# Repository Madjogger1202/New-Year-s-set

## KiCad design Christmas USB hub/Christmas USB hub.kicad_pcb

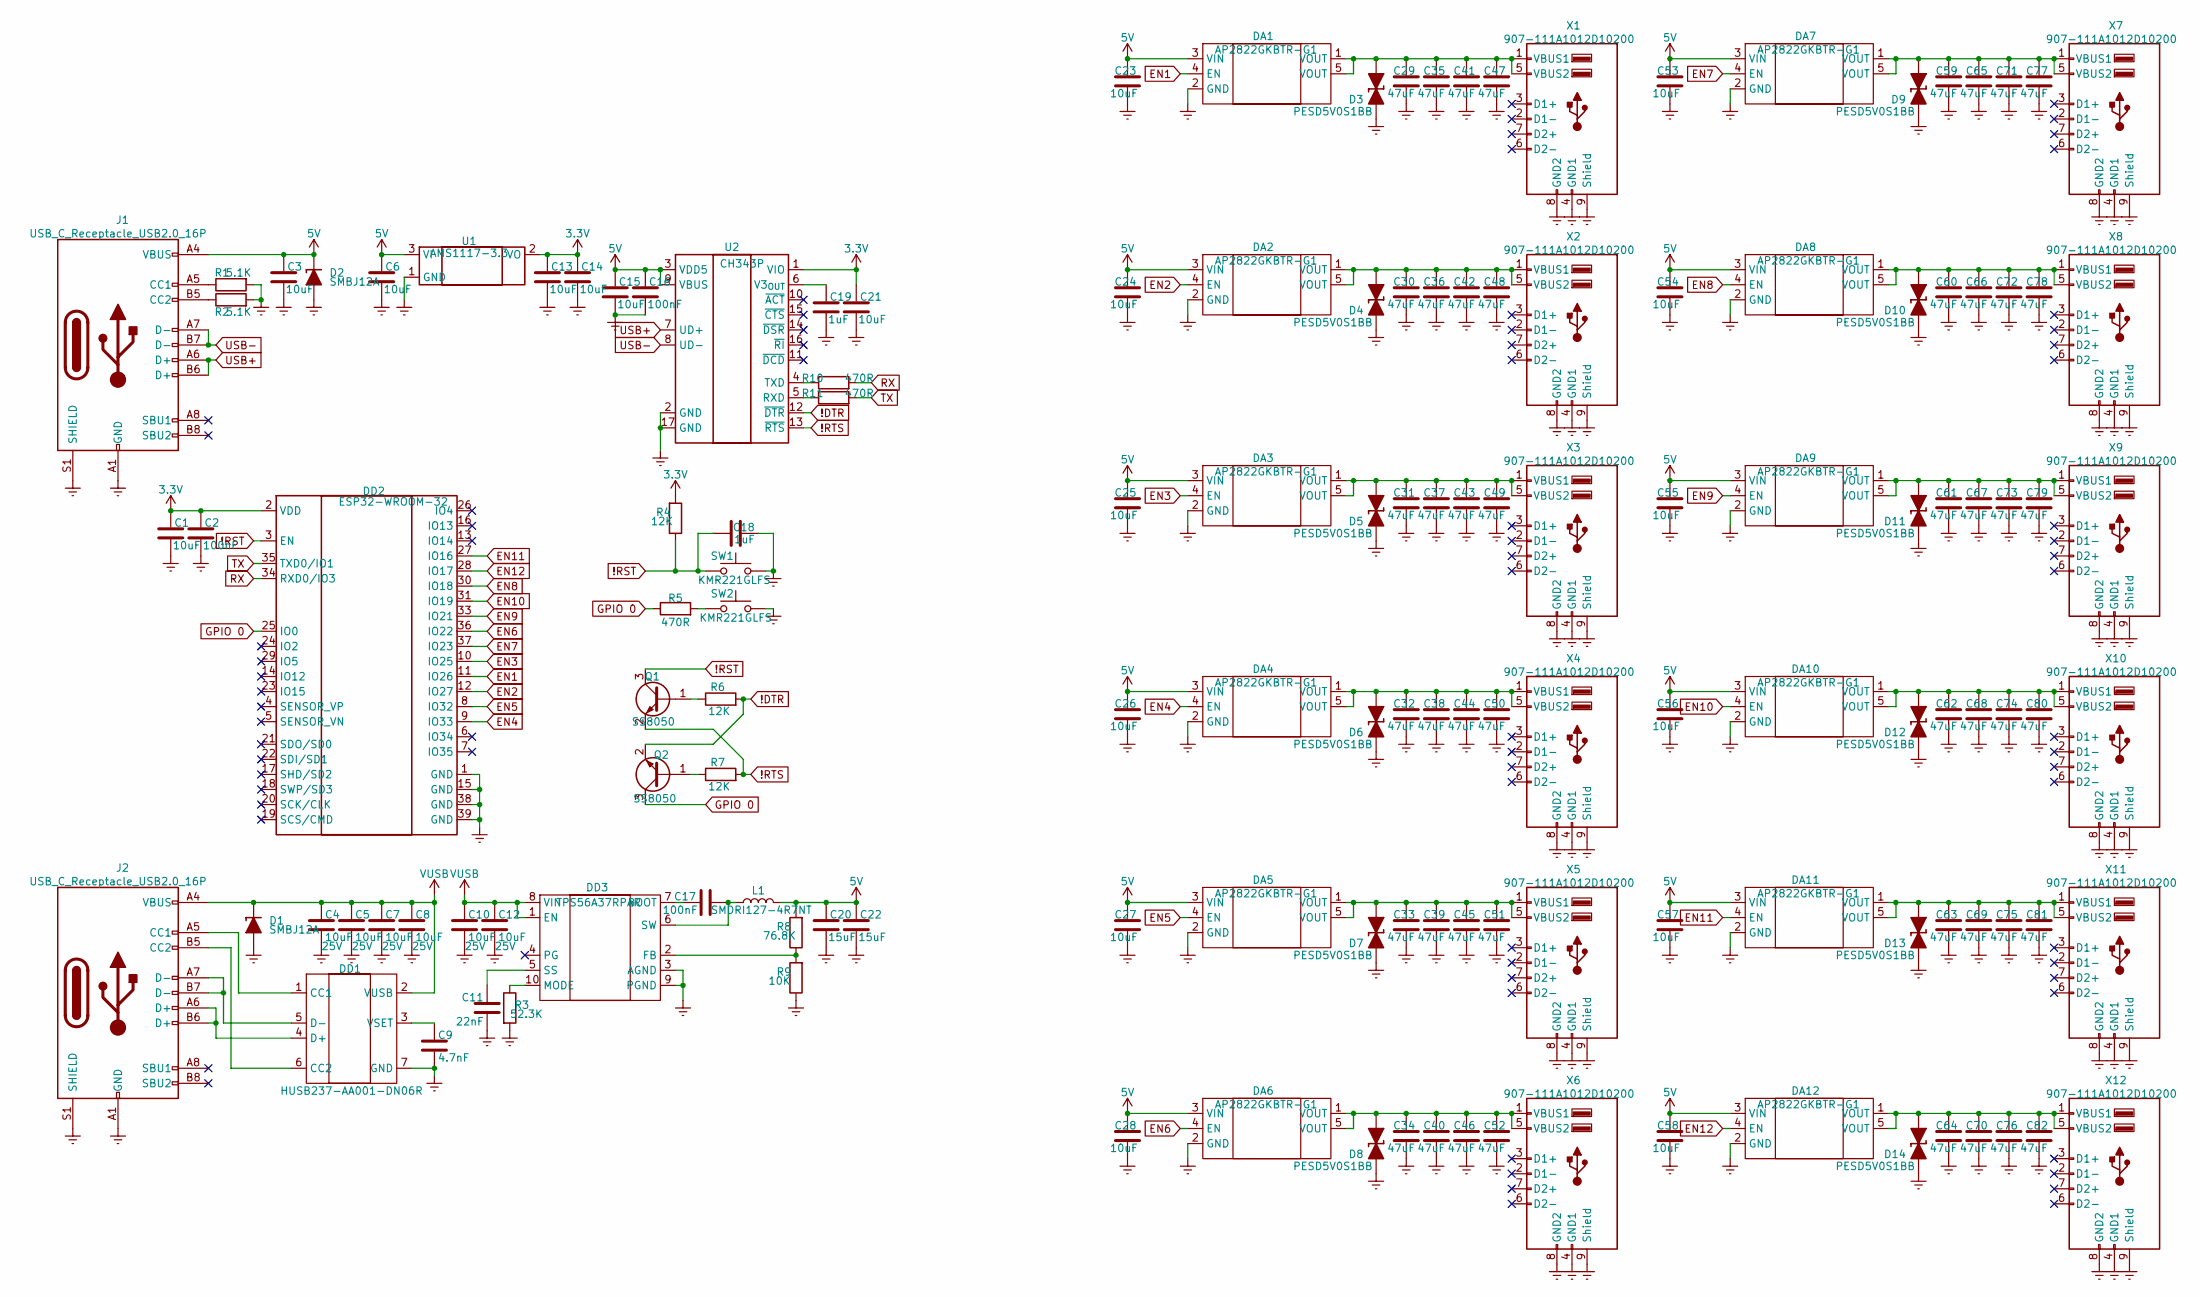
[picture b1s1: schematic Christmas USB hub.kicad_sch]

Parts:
C1, C3, C6, C13, C14, C15, C21, C23, C24, C25, C26, C27, C28, C53, C54, C55, C56, C57, C58: 10uF; C_0402_1005Metric
C2, C16, C17: 100nF; C_0402_1005Metric
C4, C5, C7, C8, C10, C12: 10uF; C_0805_2012Metric; Voltage 25V; JLCPCB part C5674
C9: 4.7nF; C_0402_1005Metric; JLCPCB part C5674
C11: 22nF; C_0402_1005Metric
C18, C19: 1uF; C_0402_1005Metric
C20, C22: 15uF; C_0402_1005Metric
C29, C30, C31, C32, C33, C34, C35, C36, C37, C38, C39, C40, C41, C42, C43, C44, C45, C46, C47, C48, C49, C50, C51, C52, C59, C60, C61, C62, C63, C64, C65, C66, C67, C68, C69, C70, C71, C72, C73, C74, C75, C76, C77, C78, C79, C80, C81, C82: 47uF; C_0603_1608Metric
D1, D2: SMBJ12A; D_SMB
D3, D4, D5, D6, D7, D8, D9, D10, D11, D12, D13, D14: PESD5V0S1BB; D_SOD-523_TVS
DA1, DA2, DA3, DA4, DA5, DA6, DA7, DA8, DA9, DA10, DA11, DA12: AP2822GKBTR-G1; SOT-23-5
DD1: HUSB237-AA001-DN06R; Manufacturer Part HUSB237-AA001-DN06R; LCSC Part Name HUSB237-AA001-DN06R
DD2: ESP32-WROOM-32
DD3: TPS56A37RPAR; Manufacturer Part TPS56A37RPAR; LCSC Part Name TPS56A37RPAR
J1, J2: USB_C_Receptacle_USB2.0_16P; USB_C_Receptacle_GCT_USB4105-xx-A_16P_TopMnt_Horizontal
L1: SMDRI127-4R7NT; L_SXN_SMDRI127
Q1, Q2: SS8050; SOT-23
R1, R2: 5.1K; R_0402_1005Metric
R3: 52.3K; R_0402_1005Metric
R4, R6, R7: 12K; R_0402_1005Metric
R5, R10, R11: 470R; R_0402_1005Metric
R8: 76.8K; R_0402_1005Metric
R9: 10K; R_0402_1005Metric
SW1, SW2: KMR221GLFS; SW_SPST_PTS810
U1: AMS1117-3.3; SOT-89-3
U2: CH343P; WCH_QFN-16-1EP_3x3mm_P0.5mm_EP1.8x1.8mm
X1, X2, X3, X4, X5, X6, X7, X8, X9, X10, X11, X12: 907-111A1012D10200; USB_A_CUI_UJ2-ADH-TH_Horizontal_Stacked

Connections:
3.3V: C1.1, C2.1, C13.1, C14.1, C21.1, DD2.2 (VDD), R4.2, U1.2 (VO), U2.1 (VIO)
5V: C3.1, C6.1, C15.1, C16.1, C20.1, C22.1, C23.1, C24.1, C25.1, C26.1, C27.1, C28.1, C53.1, C54.1, C55.1, C56.1, C57.1, C58.1, D2.1 (K), DA1.3 (VIN), DA2.3 (VIN), DA3.3 (VIN), DA4.3 (VIN), DA5.3 (VIN), DA6.3 (VIN), DA7.3 (VIN), DA8.3 (VIN), DA9.3 (VIN), DA10.3 (VIN), DA11.3 (VIN), DA12.3 (VIN), J1.A4 (VBUS), J1.A9 (VBUS), J1.B4 (VBUS), J1.B9 (VBUS), L1.2, R8.2, U1.3 (VI), U2.3 (VDD5), U2.9 (VBUS)
!DTR: Q2.2 (E), R6.2, U2.12 (~DTR)
!RST: C18.1, DD2.3 (EN), Q1.3 (C), R4.1, SW1.2
!RTS: Q1.2 (E), R7.2, U2.13 (~RTS)
EN1: DA1.4 (EN), DD2.11 (IO26)
EN2: DA2.4 (EN), DD2.12 (IO27)
EN3: DA3.4 (EN), DD2.10 (IO25)
EN4: DA4.4 (EN), DD2.9 (IO33)
EN5: DA5.4 (EN), DD2.8 (IO32)
EN6: DA6.4 (EN), DD2.36 (IO22)
EN7: DA7.4 (EN), DD2.37 (IO23)
EN8: DA8.4 (EN), DD2.30 (IO18)
EN9: DA9.4 (EN), DD2.33 (IO21)
EN10: DA10.4 (EN), DD2.31 (IO19)
EN11: DA11.4 (EN), DD2.27 (IO16)
EN12: DA12.4 (EN), DD2.28 (IO17)
Earth: C1.2, C2.2, C3.2, C4.2, C5.2, C6.2, C7.2, C8.2, C9.2, C10.2, C11.1, C12.2, C13.2, C14.2, C15.2, C16.2, C18.2, C19.2, C20.2, C21.2, C22.2, C23.2, C24.2, C25.2, C26.2, C27.2, C28.2, C29.2, C30.2, C31.2, C32.2, C33.2, C34.2, C35.2, C36.2, C37.2, C38.2, C39.2, C40.2, C41.2, C42.2, C43.2, C44.2, C45.2, C46.2, C47.2, C48.2, C49.2, C50.2, C51.2, C52.2, C53.2, C54.2, C55.2, C56.2, C57.2, C58.2, C59.2, C60.2, C61.2, C62.2, C63.2, C64.2, C65.2, C66.2, C67.2, C68.2, C69.2, C70.2, C71.2, C72.2, C73.2, C74.2, C75.2, C76.2, C77.2, C78.2, C79.2, C80.2, C81.2, C82.2, D1.2 (A), D2.2 (A), D3.1 (K), D4.1 (K), D5.1 (K), D6.1 (K), D7.1 (K), D8.1 (K), D9.1 (K), D10.1 (K), D11.1 (K), D12.1 (K), D13.1 (K), D14.1 (K), DA1.2 (GND), DA2.2 (GND), DA3.2 (GND), DA4.2 (GND), DA5.2 (GND), DA6.2 (GND), DA7.2 (GND), DA8.2 (GND), DA9.2 (GND), DA10.2 (GND), DA11.2 (GND), DA12.2 (GND), DD1.7 (GND), DD2.1 (GND), DD2.15 (GND), DD2.38 (GND), DD2.39 (GND), DD3.3 (AGND), DD3.9 (PGND), J1.A1 (GND), J1.A12 (GND), J1.B1 (GND), J1.B12 (GND), J1.S1 (SHIELD), J2.A1 (GND), J2.A12 (GND), J2.B1 (GND), J2.B12 (GND), J2.S1 (SHIELD), R1.2, R2.2, R3.2, R9.1, SW1.1, SW2.1, U1.1 (GND), U2.2 (GND), U2.17 (GND), X1.4 (GND1), X1.8 (GND2), X1.9 (Shield), X2.4 (GND1), X2.8 (GND2), X2.9 (Shield), X3.4 (GND1), X3.8 (GND2), X3.9 (Shield), X4.4 (GND1), X4.8 (GND2), X4.9 (Shield), X5.4 (GND1), X5.8 (GND2), X5.9 (Shield), X6.4 (GND1), X6.8 (GND2), X6.9 (Shield), X7.4 (GND1), X7.8 (GND2), X7.9 (Shield), X8.4 (GND1), X8.8 (GND2), X8.9 (Shield), X9.4 (GND1), X9.8 (GND2), X9.9 (Shield), X10.4 (GND1), X10.8 (GND2), X10.9 (Shield), X11.4 (GND1), X11.8 (GND2), X11.9 (Shield), X12.4 (GND1), X12.8 (GND2), X12.9 (Shield)
GPIO 0: DD2.25 (IO0), Q2.3 (C), R5.1
unnamed: C29.1, C35.1, C41.1, C47.1, D3.2 (A), DA1.1 (VOUT), DA1.5 (VOUT), X1.1 (VBUS1), X1.5 (VBUS2)
unnamed: C30.1, C36.1, C42.1, C48.1, D4.2 (A), DA2.1 (VOUT), DA2.5 (VOUT), X2.1 (VBUS1), X2.5 (VBUS2)
unnamed: C31.1, C37.1, C43.1, C49.1, D5.2 (A), DA3.1 (VOUT), DA3.5 (VOUT), X3.1 (VBUS1), X3.5 (VBUS2)
unnamed: C32.1, C38.1, C44.1, C50.1, D6.2 (A), DA4.1 (VOUT), DA4.5 (VOUT), X4.1 (VBUS1), X4.5 (VBUS2)
unnamed: C33.1, C39.1, C45.1, C51.1, D7.2 (A), DA5.1 (VOUT), DA5.5 (VOUT), X5.1 (VBUS1), X5.5 (VBUS2)
unnamed: C34.1, C40.1, C46.1, C52.1, D8.2 (A), DA6.1 (VOUT), DA6.5 (VOUT), X6.1 (VBUS1), X6.5 (VBUS2)
unnamed: C59.1, C65.1, C71.1, C77.1, D9.2 (A), DA7.1 (VOUT), DA7.5 (VOUT), X7.1 (VBUS1), X7.5 (VBUS2)
unnamed: C60.1, C66.1, C72.1, C78.1, D10.2 (A), DA8.1 (VOUT), DA8.5 (VOUT), X8.1 (VBUS1), X8.5 (VBUS2)
unnamed: C61.1, C67.1, C73.1, C79.1, D11.2 (A), DA9.1 (VOUT), DA9.5 (VOUT), X9.1 (VBUS1), X9.5 (VBUS2)
unnamed: C62.1, C68.1, C74.1, C80.1, D12.2 (A), DA10.1 (VOUT), DA10.5 (VOUT), X10.1 (VBUS1), X10.5 (VBUS2)
unnamed: C63.1, C69.1, C75.1, C81.1, D13.2 (A), DA11.1 (VOUT), DA11.5 (VOUT), X11.1 (VBUS1), X11.5 (VBUS2)
unnamed: C64.1, C70.1, C76.1, C82.1, D14.2 (A), DA12.1 (VOUT), DA12.5 (VOUT), X12.1 (VBUS1), X12.5 (VBUS2)
unnamed: DD1.1 (CC1), J2.A5 (CC1)
unnamed: DD1.6 (CC2), J2.B5 (CC2)
unnamed: DD1.4 (D+), J2.A6 (D+), J2.B6 (D+)
unnamed: DD1.5 (D-), J2.A7 (D-), J2.B7 (D-)
unnamed: C9.1, DD1.3 (VSET)
unnamed: C17.1, DD3.7 (BOOT)
unnamed: DD3.2 (FB), R8.1, R9.2
unnamed: DD3.10 (MODE), R3.1
unnamed: C11.2, DD3.5 (SS)
unnamed: C17.2, DD3.6 (SW), L1.1
unnamed: J1.A5 (CC1), R1.1
unnamed: J1.B5 (CC2), R2.1
unnamed: Q1.1 (B), R6.1
unnamed: Q2.1 (B), R7.1
unnamed: R5.2, SW2.2
unnamed: R11.1, U2.5 (RXD)
unnamed: R10.1, U2.4 (TXD)
unnamed: C19.1, U2.6 (V3_{OUT})
RX: DD2.34 (RXD0/IO3), R10.2
TX: DD2.35 (TXD0/IO1), R11.2
USB+: J1.A6 (D+), J1.B6 (D+), U2.7 (UD+)
USB-: J1.A7 (D-), J1.B7 (D-), U2.8 (UD-)
VUSB: C4.1, C5.1, C7.1, C8.1, C10.1, C12.1, D1.1 (K), DD1.2 (VUSB), DD3.1 (EN), DD3.8 (VIN), J2.A4 (VBUS), J2.A9 (VBUS), J2.B4 (VBUS), J2.B9 (VBUS)

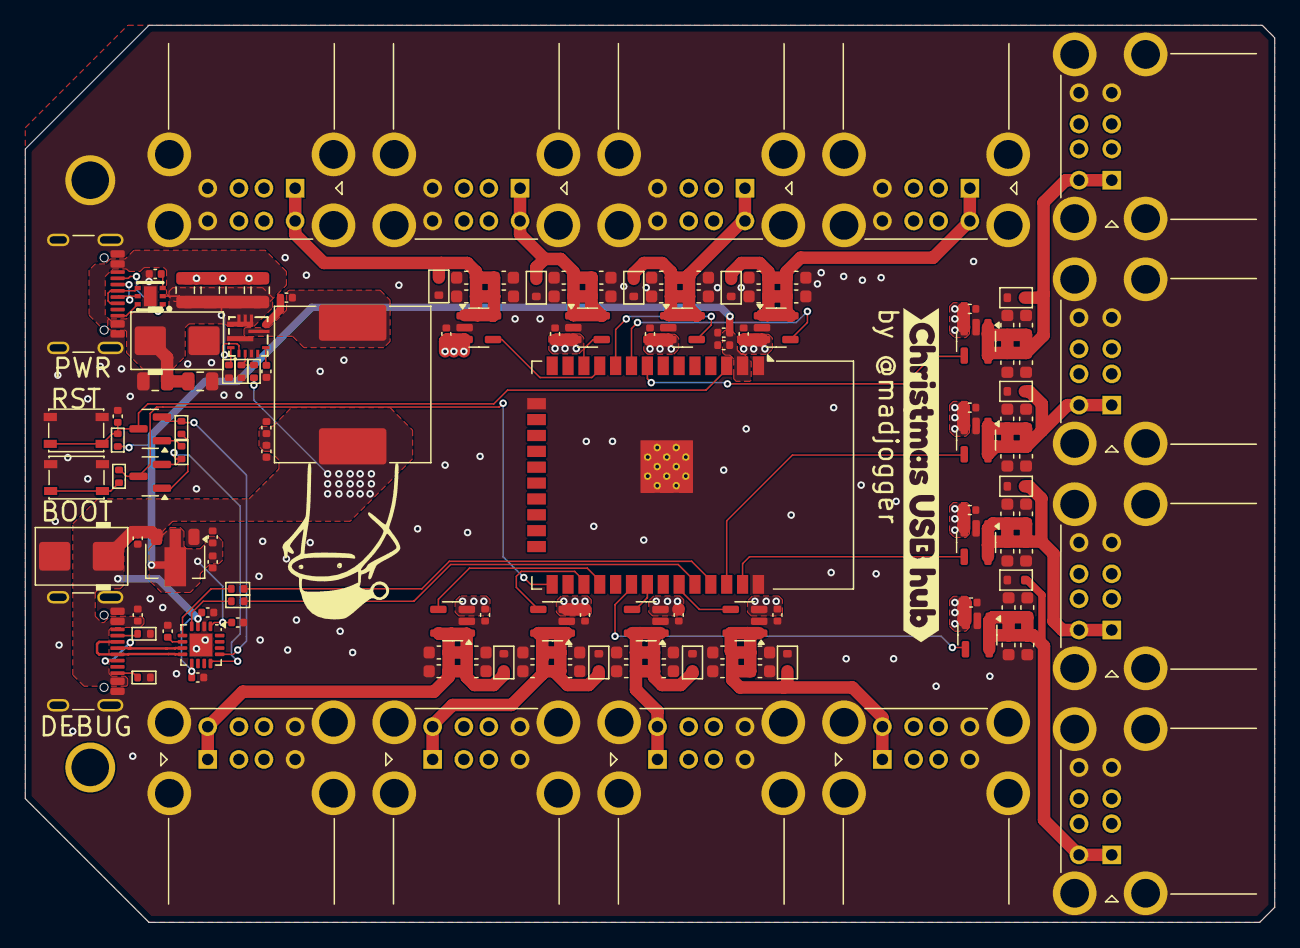
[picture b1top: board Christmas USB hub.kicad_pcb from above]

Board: 2 copper layers, 100.0 x 71.8 mm, 144 parts (0 on the bottom side), 54 nets.

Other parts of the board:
kibuzzard-69519964: G***; kibuzzard-69519964

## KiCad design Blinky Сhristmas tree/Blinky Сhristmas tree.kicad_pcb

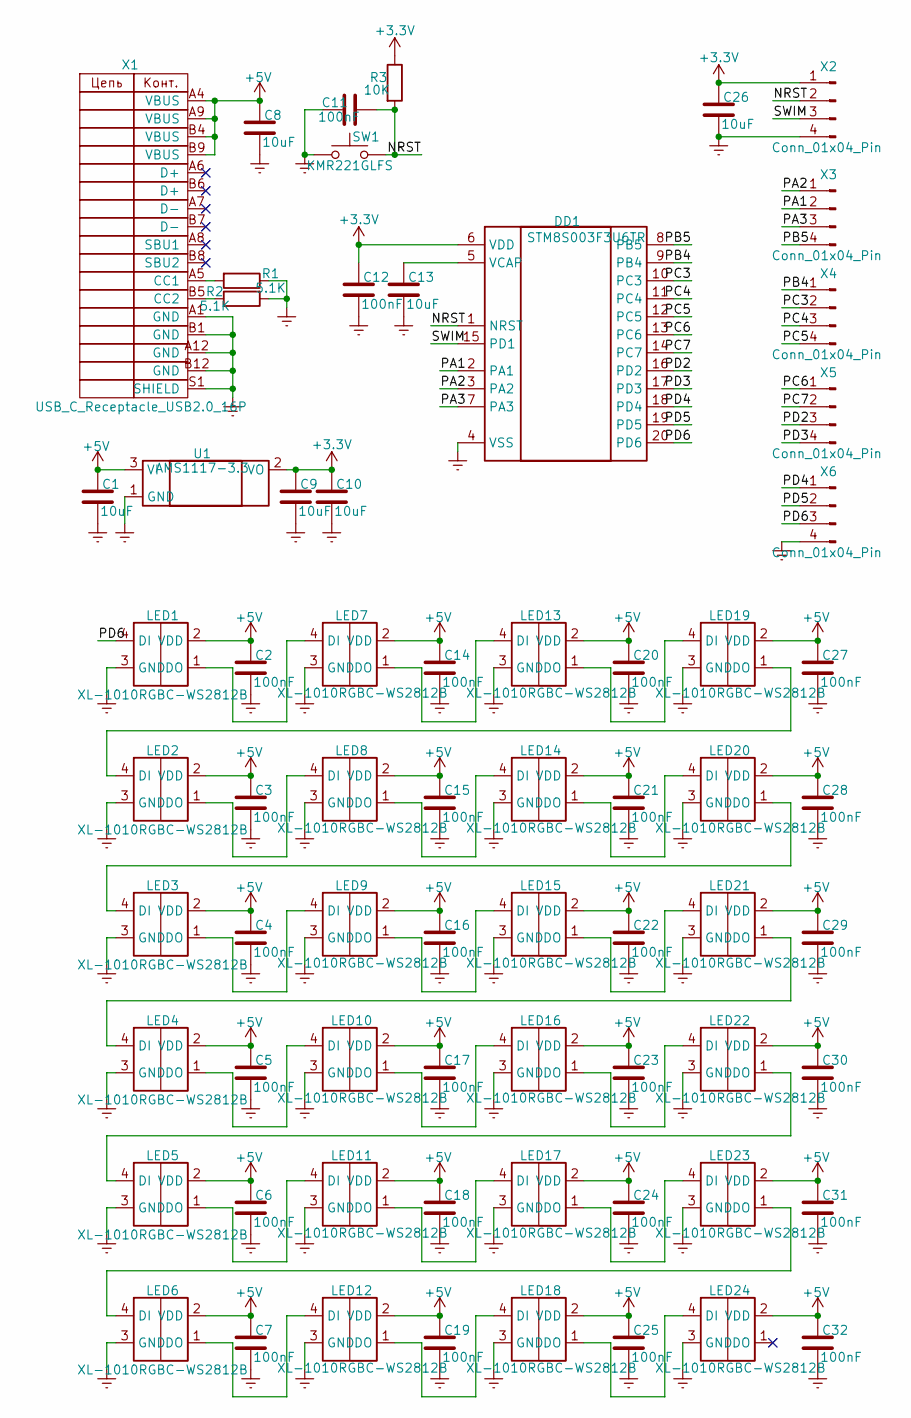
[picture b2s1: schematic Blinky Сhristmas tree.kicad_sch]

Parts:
C1, C8, C9, C10, C13, C26: 10uF; C_0402_1005Metric
C2, C3, C4, C5, C6, C7, C11, C12, C14, C15, C16, C17, C18, C19, C20, C21, C22, C23, C24, C25, C27, C28, C29, C30, C31, C32: 100nF; C_0402_1005Metric
DD1: STM8S003F3U6TR; ST_UFQFPN-20_3x3mm_P0.5mm
LED1, LED2, LED3, LED4, LED5, LED6, LED7, LED8, LED9, LED10, LED11, LED12, LED13, LED14, LED15, LED16, LED17, LED18, LED19, LED20, LED21, LED22, LED23, LED24: XL-1010RGBC-WS2812B; XL1010RGBCWS2812B; Manufacturer_Part_Number XL-1010RGBC-WS2812B
R1, R2: 5.1K; R_0402_1005Metric
R3: 10K; R_0402_1005Metric
SW1: KMR221GLFS; SW_SPST_PTS810
U1: AMS1117-3.3; SOT-89-3
X1: USB_C_Receptacle_USB2.0_16P; USB_C_Receptacle_GCT_USB4105-xx-A_16P_TopMnt_Horizontal
X2, X3, X4, X5, X6: Conn_01x04_Pin; PinHeader_1x04_P2.54mm_Vertical

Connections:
+3.3V: C9.1, C10.1, C12.1, C26.1, DD1.6 (VDD), R3.1, U1.2 (VO), X2.1
+5V: C1.1, C2.1, C3.1, C4.1, C5.1, C6.1, C7.1, C8.1, C14.1, C15.1, C16.1, C17.1, C18.1, C19.1, C20.1, C21.1, C22.1, C23.1, C24.1, C25.1, C27.1, C28.1, C29.1, C30.1, C31.1, C32.1, LED1.2 (VDD), LED2.2 (VDD), LED3.2 (VDD), LED4.2 (VDD), LED5.2 (VDD), LED6.2 (VDD), LED7.2 (VDD), LED8.2 (VDD), LED9.2 (VDD), LED10.2 (VDD), LED11.2 (VDD), LED12.2 (VDD), LED13.2 (VDD), LED14.2 (VDD), LED15.2 (VDD), LED16.2 (VDD), LED17.2 (VDD), LED18.2 (VDD), LED19.2 (VDD), LED20.2 (VDD), LED21.2 (VDD), LED22.2 (VDD), LED23.2 (VDD), LED24.2 (VDD), U1.3 (VI), X1.A4 (VBUS), X1.A9 (VBUS), X1.B4 (VBUS), X1.B9 (VBUS)
/NRST: C11.1, DD1.1 (NRST), R3.2, SW1.2, X2.2
/PA1: DD1.2 (PA1), X3.2
/PA2: DD1.3 (PA2), X3.1
/PA3: DD1.7 (PA3), X3.3
/PB4: DD1.9 (PB4), X4.1
/PB5: DD1.8 (PB5), X3.4
/PD2: DD1.16 (PD2), X5.3
/PD3: DD1.17 (PD3), X5.4
/PD4: DD1.18 (PD4), X6.1
/PD5: DD1.19 (PD5), X6.2
/PD6: DD1.20 (PD6), LED1.4 (DI), X6.3
/PС3: DD1.10 (PC3), X4.2
/PС4: DD1.11 (PC4), X4.3
/PС5: DD1.12 (PC5), X4.4
/PС6: DD1.13 (PC6), X5.1
/PС7: DD1.14 (PC7), X5.2
/SWIM: DD1.15 (PD1), X2.3
Earth: C1.2, C2.2, C3.2, C4.2, C5.2, C6.2, C7.2, C8.2, C9.2, C10.2, C11.2, C12.2, C13.2, C14.2, C15.2, C16.2, C17.2, C18.2, C19.2, C20.2, C21.2, C22.2, C23.2, C24.2, C25.2, C26.2, C27.2, C28.2, C29.2, C30.2, C31.2, C32.2, DD1.4 (VSS), LED1.3 (GND), LED2.3 (GND), LED3.3 (GND), LED4.3 (GND), LED5.3 (GND), LED6.3 (GND), LED7.3 (GND), LED8.3 (GND), LED9.3 (GND), LED10.3 (GND), LED11.3 (GND), LED12.3 (GND), LED13.3 (GND), LED14.3 (GND), LED15.3 (GND), LED16.3 (GND), LED17.3 (GND), LED18.3 (GND), LED19.3 (GND), LED20.3 (GND), LED21.3 (GND), LED22.3 (GND), LED23.3 (GND), LED24.3 (GND), R1.1, R2.2, SW1.1, U1.1 (GND), X1.A1 (GND), X1.A12 (GND), X1.B1 (GND), X1.B12 (GND), X1.S1 (SHIELD), X2.4, X6.4
unnamed: C13.1, DD1.5 (VCAP)
unnamed: LED1.1 (DO), LED7.4 (DI)
unnamed: LED2.1 (DO), LED8.4 (DI)
unnamed: LED3.1 (DO), LED9.4 (DI)
unnamed: LED4.1 (DO), LED10.4 (DI)
unnamed: LED10.1 (DO), LED16.4 (DI)
unnamed: LED5.1 (DO), LED11.4 (DI)
unnamed: LED11.1 (DO), LED17.4 (DI)
unnamed: LED6.1 (DO), LED12.4 (DI)
unnamed: LED12.1 (DO), LED18.4 (DI)
unnamed: LED7.1 (DO), LED13.4 (DI)
unnamed: LED13.1 (DO), LED19.4 (DI)
unnamed: LED8.1 (DO), LED14.4 (DI)
unnamed: LED14.1 (DO), LED20.4 (DI)
unnamed: LED9.1 (DO), LED15.4 (DI)
unnamed: LED15.1 (DO), LED21.4 (DI)
unnamed: LED16.1 (DO), LED22.4 (DI)
unnamed: LED17.1 (DO), LED23.4 (DI)
unnamed: LED18.1 (DO), LED24.4 (DI)
unnamed: LED2.4 (DI), LED19.1 (DO)
unnamed: LED3.4 (DI), LED20.1 (DO)
unnamed: LED4.4 (DI), LED21.1 (DO)
unnamed: LED5.4 (DI), LED22.1 (DO)
unnamed: LED6.4 (DI), LED23.1 (DO)
unnamed: R1.2, X1.A5 (CC1)
unnamed: R2.1, X1.B5 (CC2)

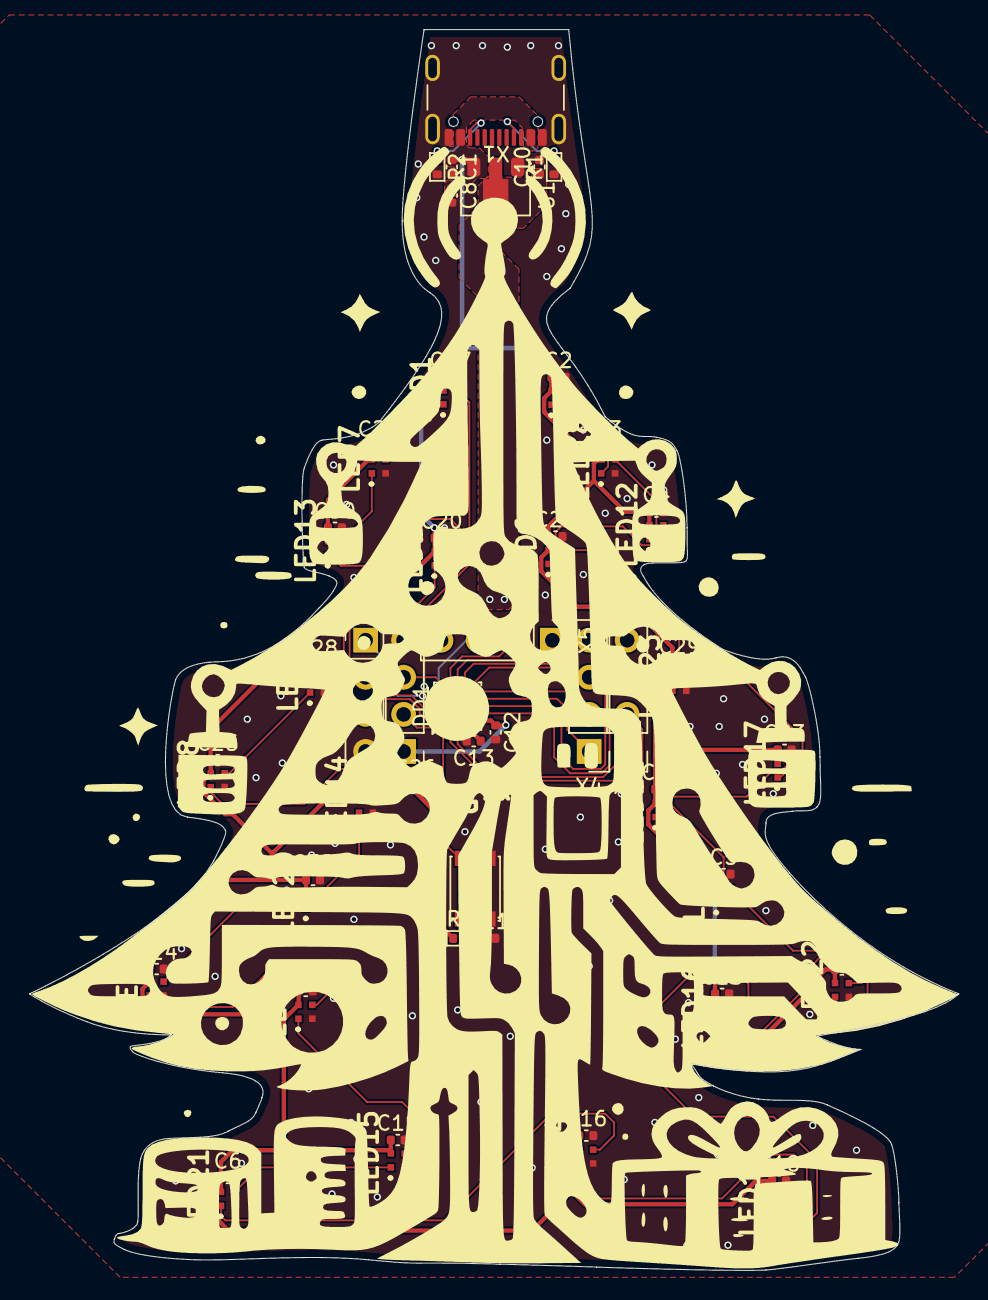
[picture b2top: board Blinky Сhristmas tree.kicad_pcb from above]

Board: 2 copper layers, 63.6 x 84.9 mm, 68 parts (0 on the bottom side), 46 nets.

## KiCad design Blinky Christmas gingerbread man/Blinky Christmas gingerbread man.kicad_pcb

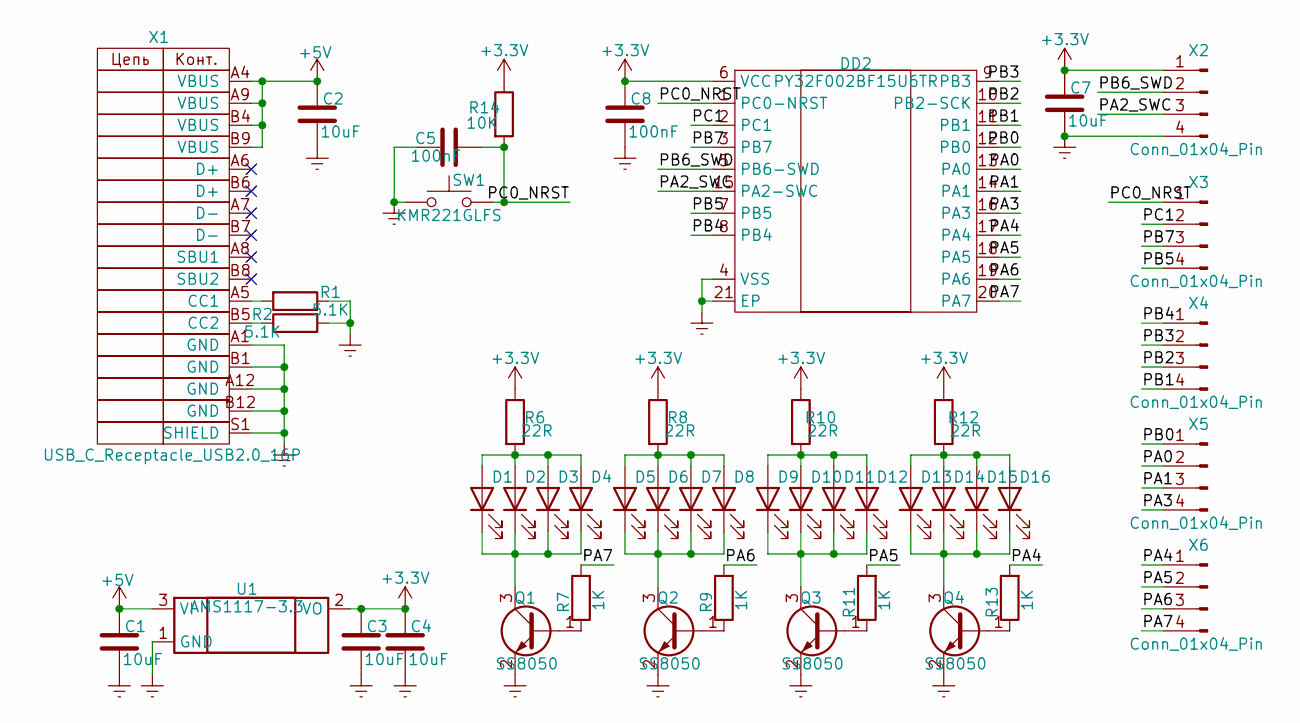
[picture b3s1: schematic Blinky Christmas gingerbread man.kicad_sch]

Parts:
C1, C2, C3, C4, C7: 10uF; C_0402_1005Metric
C5, C8: 100nF; C_0402_1005Metric
D1, D2, D3, D4, D5, D6, D7, D8, D9, D10, D11, D12, D13, D14, D15, D16: LED 0402; LED_0402_1005Metric
DD2: PY32F002BF15U6TR; Manufacturer Part PY32F002BF15U6TR; LCSC Part Name 32位ARMCortex-M0+微控制器
Q1, Q2, Q3, Q4: SS8050; SOT-23
R1, R2: 5.1K; R_0402_1005Metric
R6, R8, R10, R12: 22R; R_0603_1608Metric
R7, R9, R11, R13: 1K; R_0402_1005Metric
R14: 10K; R_0402_1005Metric
SW1: KMR221GLFS; SW_SPST_PTS810
U1: AMS1117-3.3; SOT-89-3
X1: USB_C_Receptacle_USB2.0_16P; USB_C_Receptacle_GCT_USB4105-xx-A_16P_TopMnt_Horizontal
X2, X3, X4, X5, X6: Conn_01x04_Pin; PinHeader_1x04_P2.54mm_Vertical

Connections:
+3.3V: C3.1, C4.1, C7.1, C8.1, DD2.6 (VCC), R6.1, R8.1, R10.1, R12.1, R14.1, U1.2 (VO), X2.1
+5V: C1.1, C2.1, U1.3 (VI), X1.A4 (VBUS), X1.A9 (VBUS), X1.B4 (VBUS), X1.B9 (VBUS)
/PA0: DD2.13 (PA0), X5.2
/PA1: DD2.14 (PA1), X5.3
/PA2_SWC: DD2.15 (PA2-SWC), X2.3
/PA3: DD2.16 (PA3), X5.4
/PA4: DD2.17 (PA4), R13.2, X6.1
/PA5: DD2.18 (PA5), R11.2, X6.2
/PA6: DD2.19 (PA6), R9.2, X6.3
/PA7: DD2.20 (PA7), R7.2, X6.4
/PB0: DD2.12 (PB0), X5.1
/PB1: DD2.11 (PB1), X4.4
/PB2: DD2.10 (PB2-SCK), X4.3
/PB3: DD2.9 (PB3), X4.2
/PB4: DD2.8 (PB4), X4.1
/PB5: DD2.7 (PB5), X3.4
/PB6_SWD: DD2.5 (PB6-SWD), X2.2
/PB7: DD2.3 (PB7), X3.3
/PC0_NRST: C5.1, DD2.1 (PC0-NRST), R14.2, SW1.2, X3.1
/PС1: DD2.2 (PC1), X3.2
Earth: C1.2, C2.2, C3.2, C4.2, C5.2, C7.2, C8.2, DD2.4 (VSS), DD2.21 (EP), Q1.2 (E), Q2.2 (E), Q3.2 (E), Q4.2 (E), R1.1, R2.2, SW1.1, U1.1 (GND), X1.A1 (GND), X1.A12 (GND), X1.B1 (GND), X1.B12 (GND), X1.S1 (SHIELD), X2.4
unnamed: D1.2 (A), D2.2 (A), D3.2 (A), D4.2 (A), R6.2
unnamed: D1.1 (K), D2.1 (K), D3.1 (K), D4.1 (K), Q1.3 (C)
unnamed: D5.2 (A), D6.2 (A), D7.2 (A), D8.2 (A), R8.2
unnamed: D5.1 (K), D6.1 (K), D7.1 (K), D8.1 (K), Q2.3 (C)
unnamed: D9.2 (A), D10.2 (A), D11.2 (A), D12.2 (A), R10.2
unnamed: D9.1 (K), D10.1 (K), D11.1 (K), D12.1 (K), Q3.3 (C)
unnamed: D13.2 (A), D14.2 (A), D15.2 (A), D16.2 (A), R12.2
unnamed: D13.1 (K), D14.1 (K), D15.1 (K), D16.1 (K), Q4.3 (C)
unnamed: Q1.1 (B), R7.1
unnamed: Q2.1 (B), R9.1
unnamed: Q3.1 (B), R11.1
unnamed: Q4.1 (B), R13.1
unnamed: R1.2, X1.A5 (CC1)
unnamed: R2.1, X1.B5 (CC2)

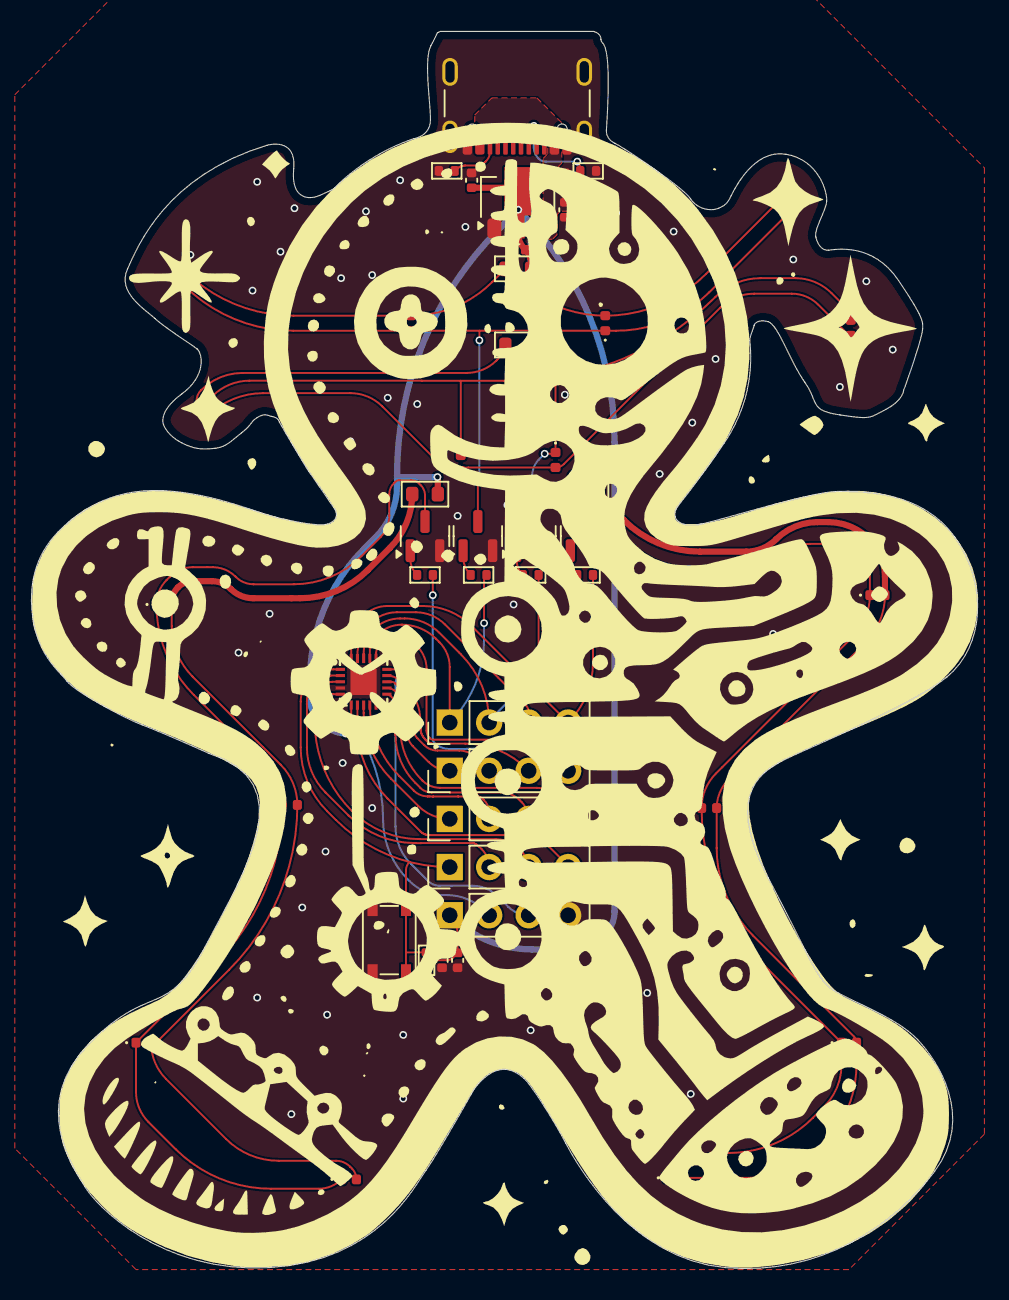
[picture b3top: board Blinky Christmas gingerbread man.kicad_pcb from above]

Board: 2 copper layers, 60.9 x 79.6 mm, 47 parts (0 on the bottom side), 35 nets.

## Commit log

2025-12-27 rev0 ready
2025-12-27 Blinky Christmas gingerbread man rev0
2025-12-27 Blinky Сhristmas tree rev0 ready
2025-12-28 Christmas USB hub rev0 ready
